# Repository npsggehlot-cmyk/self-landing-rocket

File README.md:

# Self-Landing TVC Rocket

This is my build log and source repository for a 3-inch model rocket that steers itself with a thrust-vectored motor and is designed to land on its own legs. Everything is here: the custom flight computer (RocketFC), the 3D-printed avionics bay, the servo-driven parachute ejector, the flight software, and the simulators I use to test ideas before flying them.

**Current status:** Flight computer v2.1 is ordered from JLCPCB, fully assembled. The firmware is written and has been tested in simulation. The avionics bay and chute ejector are designed and ready to print. Next up is bench testing once the boards arrive, followed by a first flight using the parachute.

| Flight computer (top) | Avionics bay | 3D flight simulator |
|---|---|---|
|  |  |  |

---

## Mission profile

```mermaid
flowchart LR
    A[On the pad<br/>self-test beeps] -->|F15 #1 lit by<br/>launch controller| B[Boost<br/>TVC holds vertical]
    B -->|burnout at ~3.5 s| C[Coast]
    C -->|apogee| D{Flight mode}
    D -->|chute test| E[Servo releases the<br/>spring ejector and chute]
    D -->|landing| F[Free fall]
    F -->|timed so the burn<br/>ends at the ground| G[F15 #2 landing burn<br/>TVC on, legs released]
    E --> H[Legs released below 20 m]
    G --> I[Touchdown<br/>log closed, locator beeps]
    H --> I
```

## What's in this repo

| Folder | Contents | Start here |
|---|---|---|
| [`hardware/flight-computer`](hardware/flight-computer) | RocketFC v2.1, a 70 mm round 4-layer PCB designed in KiCad | `rocket_fc.kicad_pro`, plus Gerbers, BOM and CPL in `fabrication/` |
| [`hardware/avionics-bay`](hardware/avionics-bay) | Printed sled for the Apogee 3" tube, held in place by 8 radial M3 screws | STL and STEP files, tube drill template |
| [`hardware/chute-ejector`](hardware/chute-ejector) | Spring-loaded piston released by a servo-driven latch | Print-ready STLs |
| [`firmware/RocketFC`](firmware/RocketFC) | Arduino Nano flight software: TVC control, flight events, SD logging | `RocketFC.ino` |
| [`simulation/matlab`](simulation/matlab) | Interactive 3D flight simulator for tuning the PID gains and landing delay | `rocketSim3D.m` |
| [`simulation/firmware-sim`](simulation/firmware-sim) | Runs the actual flight firmware on a PC against simulated sensors | `sim.cpp` |
| [`LOG.md`](LOG.md) | Engineering log with a dated entry for each work session | |

## Flight computer overview

```
2S LiPo (XT30) ──┬── diode ── POWER switch ── Nano VIN + 3.3 V (sensors, SD card)
                 ├── 5 V 3 A buck, enabled by the switch ── 3 servos + buzzer
                 └── ARM plug (XT30) ── 4 low-side pyro channels (WAGO lever terminals)
```

| Function | Nano pin | Notes |
|---|---|---|
| Pyro P1 ascent, P2 landing, P3 legs, P4 spare | D2, D4, D6, D8 | AO3400A MOSFETs with 100k gate pull-downs; only live when the ARM plug is in |
| Continuity P1 to P4 | A0 to A3 | About 2.1 V when armed with an igniter connected, about 1.2 V when disarmed, 0 V when open |
| Servo X, servo Y (TVC), AUX (chute) | D3, D5, D7 | Powered from a separate 5 V buck converter |
| Battery and arm sense | A6, A7 | Battery voltage = A6 reading × 4.03 |
| IMU LSM6DSO32 (±32 g) and barometer MS5607 | I²C at 0x6A and 0x77 | Level-shifted to the 5 V Nano |
| microSD card (hinged lid) | SPI, D10 to D13 | Buffered through a 74LVC125 |
| Buzzer | D9 | Magnetic transducer, so it needs a tone rather than a steady signal |

Before ordering, the design passed a full design rule check with no errors, a pad-by-pad comparison between the schematic and the PCB (282 of 282 connections matched), an electrical rules check with no errors, and all 34 BOM lines were matched to parts in stock at JLCPCB.

## Key numbers

| | |
|---|---|
| Body tube | Apogee 3" (74.47 mm inner diameter); the bay and sled are 74.0 mm |
| Motors | 2 × Estes F15 (49.6 N·s total impulse, 25.3 N peak, 3.45 s burn) |
| Battery | 2S LiPo, 1000 mAh, 70 × 35 × 18 mm, XT30 connector |
| Simulated apogee at 1.0 kg | About 50 m |
| Best simulated landing delay | 1.76 s after apogee, with a window of roughly ±0.01 s |

## Links

- Onshape model of the avionics bay: [RocketFC Avionics Bay (3in Apogee tube)](https://cad.onshape.com/documents/a77bffe2781b56247ce74af7/w/bac2e3535b987d098c97ed26/e/773c68a36321aff5911a4cc4)

## Roadmap

- [x] Design, verify and order the flight computer PCB
- [x] Design the avionics bay and chute ejector
- [x] Write the firmware, compile it for the ATmega328P and test it in simulation
- [x] Build the 3D flight simulator in MATLAB
- [ ] Bench test the boards when they arrive: sensors, servos, and a pyro test with a small bulb
- [ ] Print the bay and ejector and test fit them in the tube
- [ ] Static test to measure the F15 igniter delay (`fire2` command)
- [ ] Flight 1: parachute mode with TVC on the way up
- [ ] Tune the PID gains using the flight logs
- [ ] Flight 2 and beyond: propulsive landing attempts

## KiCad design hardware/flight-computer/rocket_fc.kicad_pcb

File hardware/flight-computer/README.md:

# RocketFC v2.1 flight computer PCB

Open `rocket_fc.kicad_pro` in KiCad 7 or newer.

- `fabrication/` holds exactly what was sent to JLCPCB: the Gerbers plus the full-assembly BOM and CPL files.
- `scripts/` has the Python scripts used to generate the schematic and board. `design.py` is the single source of truth for every part and net.
- `lib/` contains a local footprint for the WAGO 2601 lever terminals.

JLCPCB settings used: 4 layers, 1.6 mm, ENIG, Standard PCBA, assembly on both sides, parts placement confirmation, and depaneling.

When bringing up a new board, check the test pads first. VLOG should read about 7.9 V, VSRV 5.0 V and 3V3 3.3 V.

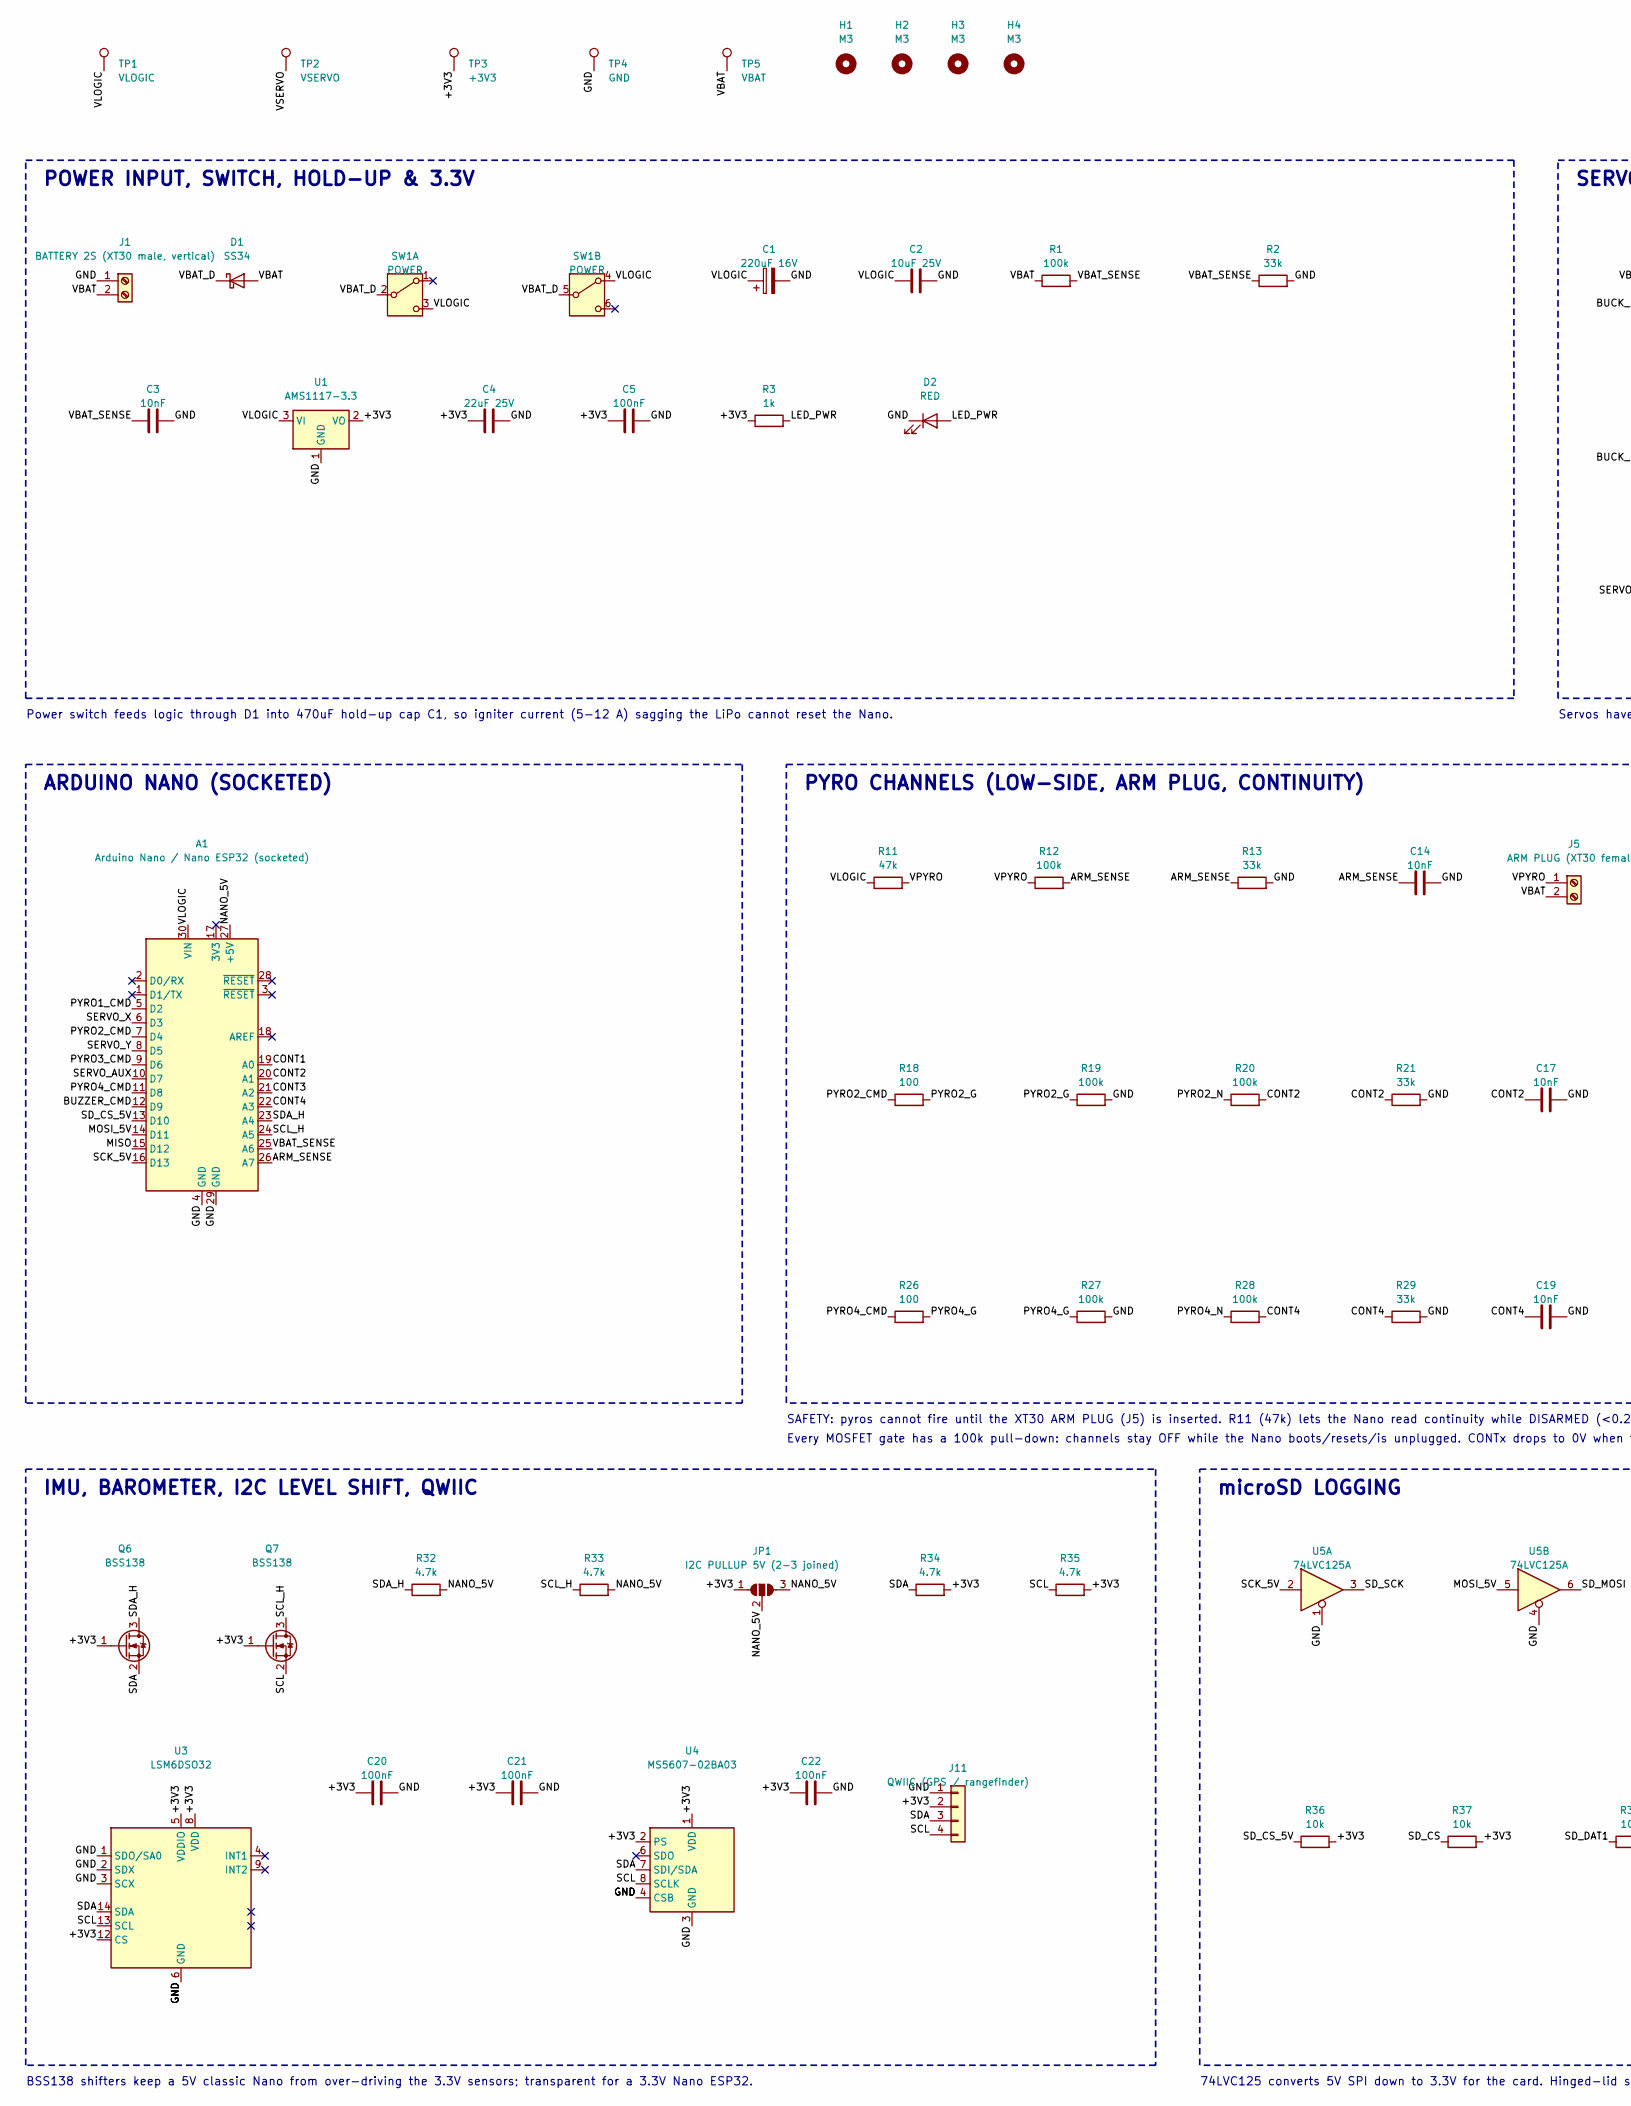
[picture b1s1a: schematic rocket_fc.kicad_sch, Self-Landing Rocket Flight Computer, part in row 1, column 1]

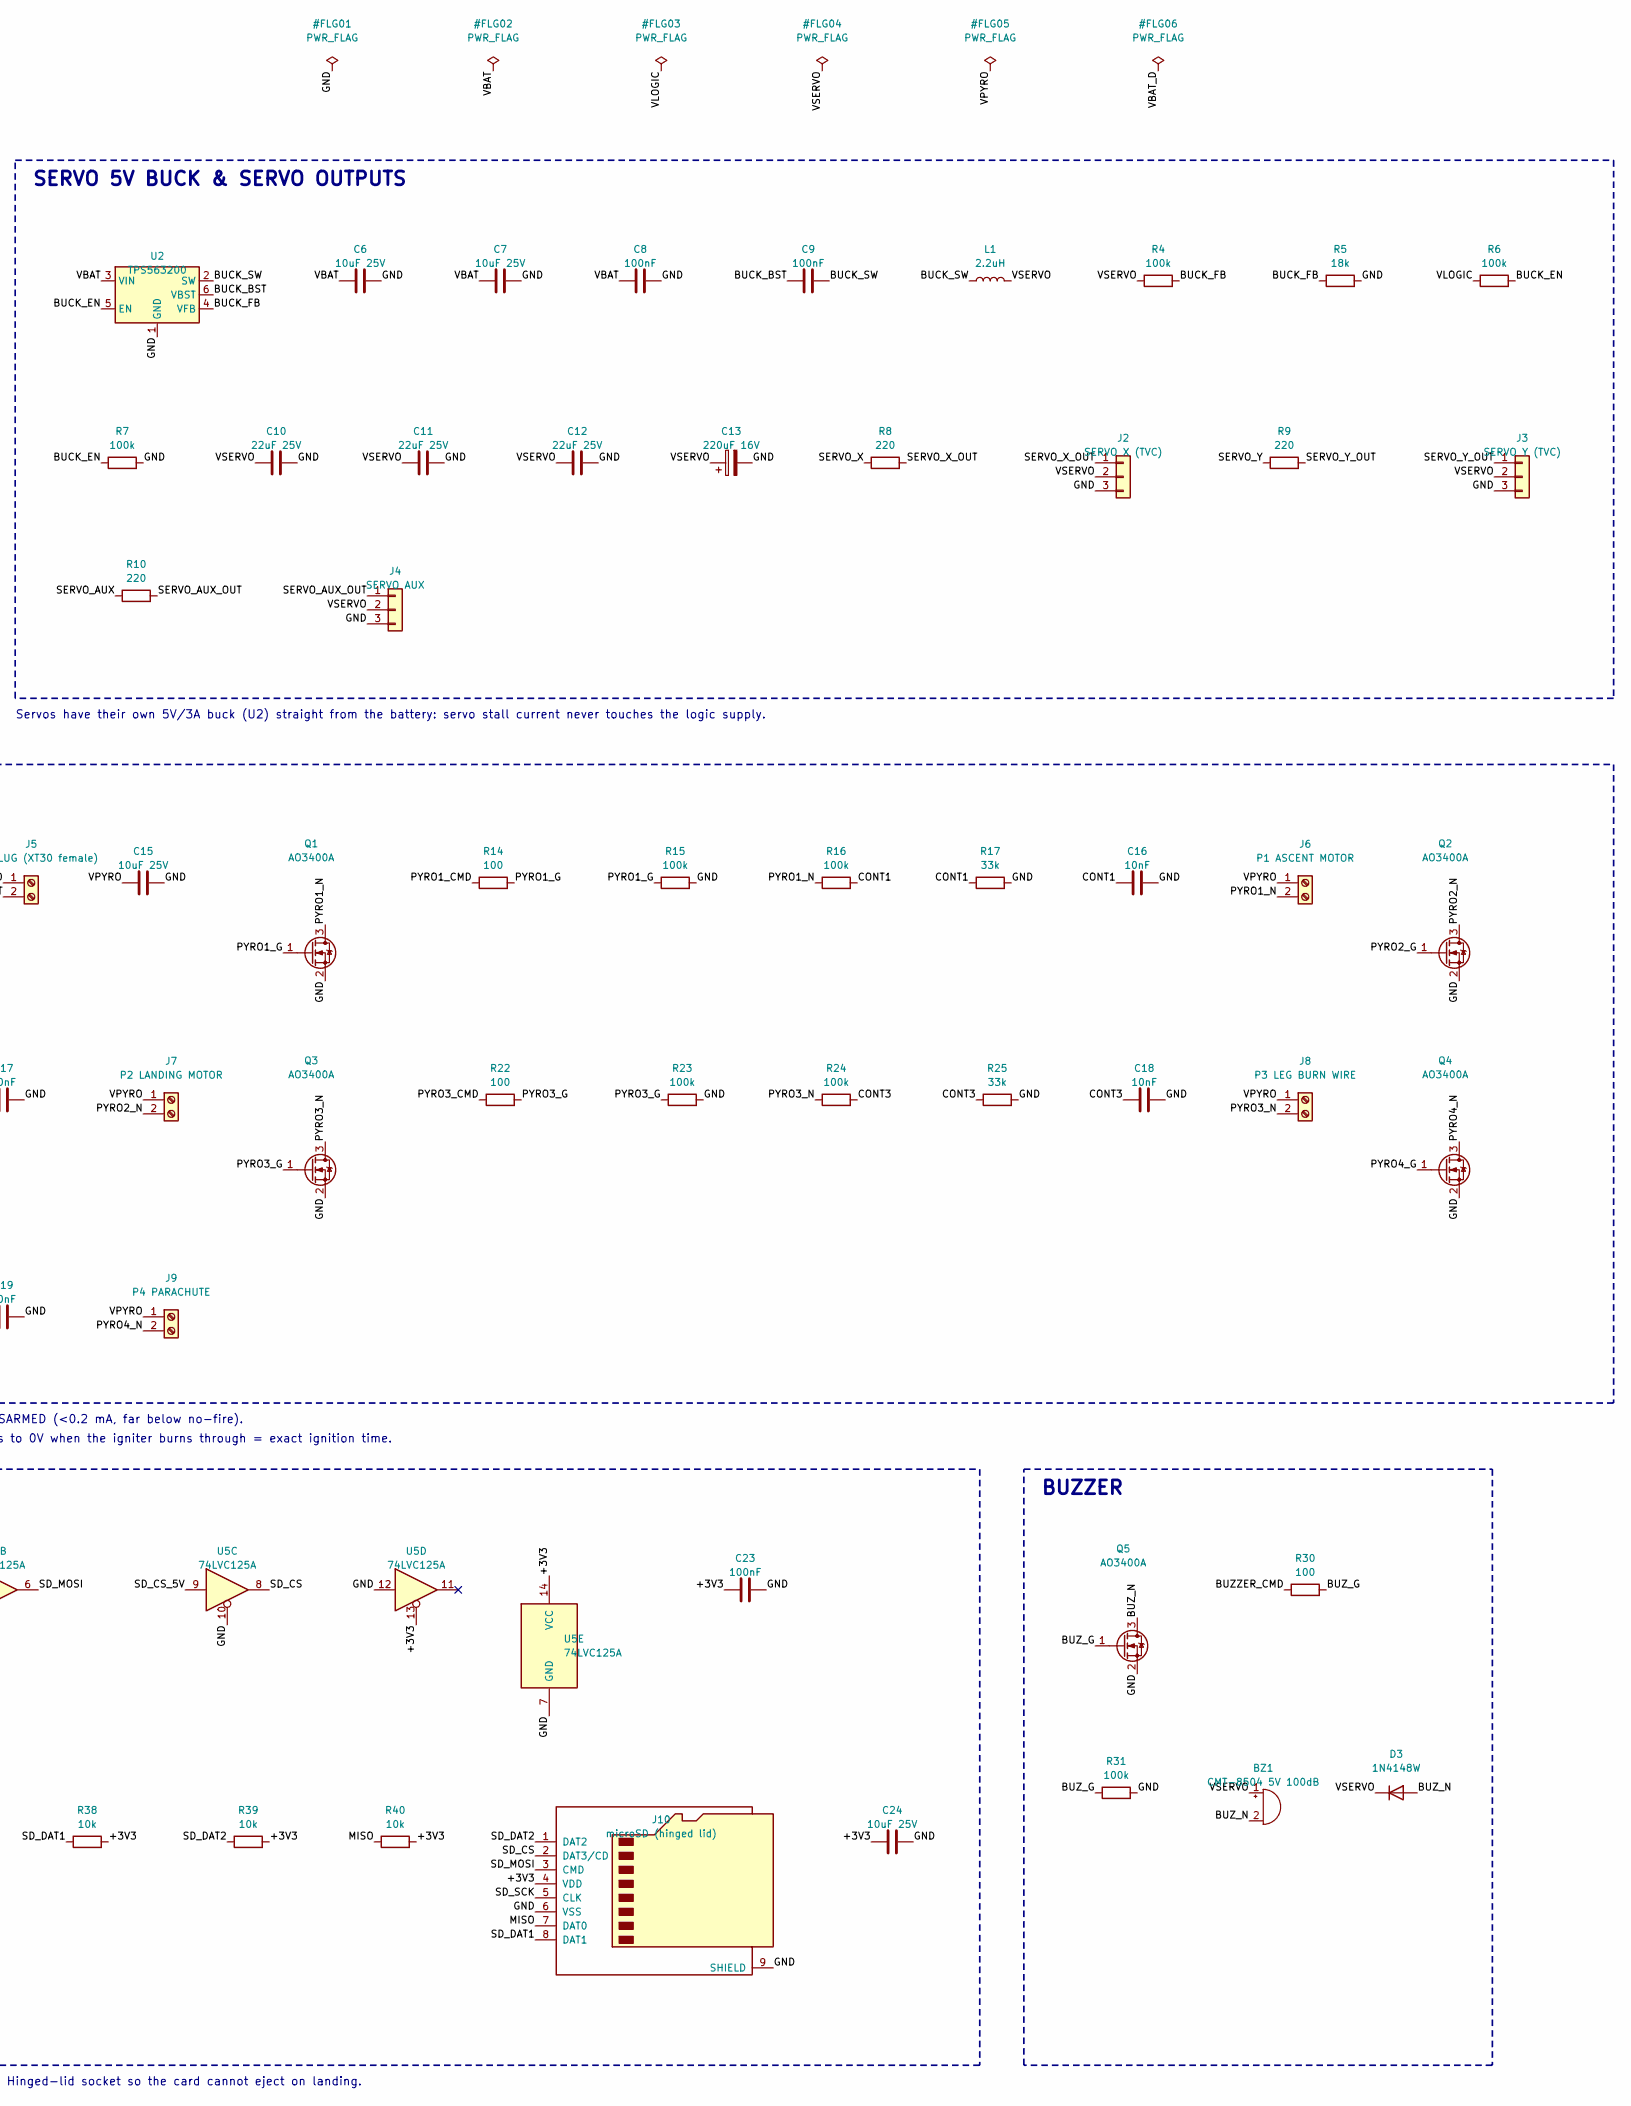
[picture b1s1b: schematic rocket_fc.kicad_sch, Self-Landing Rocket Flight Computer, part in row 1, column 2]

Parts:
A1: Arduino Nano / Nano ESP32 (socketed); Arduino_Nano; MPN 2x 1x15 2.54mm female header (socket)
BZ1: CMT-8504 5V 100dB; MagneticBuzzer_CUI_CMT-8504-100-SMT; MPN Same Sky (CUI) CMT-8504-100-SMT-TR magn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; LCSC C22359707
C1: 220uF 16V; CP_Elec_6.3x7.7; MPN Panasonic EEE-FK1C221P 220uF 16V (brown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; LCSC C178534
C2, C6, C7, C15, C24: 10uF 25V; C_0805_2012Metric; LCSC C15850
C3, C14, C16, C17, C18, C19: 10nF; C_0603_1608Metric; LCSC C57112
C4, C10, C11, C12: 22uF 25V; C_0805_2012Metric; LCSC C45783
C5, C8, C9, C20, C21, C22, C23: 100nF; C_0603_1608Metric; LCSC C14663
C13: 220uF 16V; CP_Elec_6.3x7.7; MPN Panasonic EEE-FK1C221P 220uF 16V (servo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; LCSC C178534
D1: SS34; D_SMA; MPN SS34 (40V 3A Schottky); LCSC C8678
D2: RED; LED_0603_1608Metric; MPN KT-0603R red LED; LCSC C2286
D3: 1N4148W; D_SOD-123; MPN 1N4148W; LCSC C81598
H1, H2, H3, H4: M3; MountingHole_3.2mm_M3
J1: BATTERY 2S (XT30 male, vertical); AMASS_XT30UPB-M_1x02_P5.0mm_Vertical; MPN AMASS XT30UPB-M; LCSC C428721
J2: SERVO X (TVC); PinHeader_1x03_P2.54mm_Vertical; MPN 2.54mm 1x3 male header; LCSC C49257
J3: SERVO Y (TVC); PinHeader_1x03_P2.54mm_Vertical; MPN 2.54mm 1x3 male header; LCSC C49257
J4: SERVO AUX; PinHeader_1x03_P2.54mm_Vertical; MPN 2.54mm 1x3 male header; LCSC C49257
J5: ARM PLUG (XT30 female); AMASS_XT30PW-F_1x02_P2.50mm_Horizontal; MPN AMASS XT30PW-F; LCSC C2913282
J6: P1 ASCENT MOTOR; TerminalBlock_WAGO_2601-3102_1x02_P3.50mm_Vertical; MPN WAGO 2601-3102 (lever); LCSC C20252913
J7: P2 LANDING MOTOR; TerminalBlock_WAGO_2601-3102_1x02_P3.50mm_Vertical; MPN WAGO 2601-3102 (lever); LCSC C20252913
J8: P3 LEG BURN WIRE; TerminalBlock_WAGO_2601-3102_1x02_P3.50mm_Vertical; MPN WAGO 2601-3102 (lever); LCSC C20252913
J9: P4 PARACHUTE; TerminalBlock_WAGO_2601-3102_1x02_P3.50mm_Vertical; MPN WAGO 2601-3102 (lever); LCSC C20252913
J10: microSD (hinged lid); microSD_HC_Molex_47219-2001; MPN Molex 47219-2001 (hinge lid - will not 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; LCSC C164170
J11: QWIIC (GPS / rangefinder); JST_SH_SM04B-SRSS-TB_1x04-1MP_P1.00mm_Horizontal; MPN JST SM04B-SRSS-TB; LCSC C160404
JP1: I2C PULLUP 5V (2-3 joined); SolderJumper-3_P1.3mm_Open_RoundedPad1.0x1.5mm; MPN solder jumper (no part)
L1: 2.2uH; L_Bourns_SRN6045TA; MPN Bourns SRN6045TA-2R2Y (2.2uH, 6A); LCSC C1332316
Q1, Q2, Q3, Q4, Q5: AO3400A; SOT-23; MPN AO3400A; LCSC C20917
Q6, Q7: BSS138; SOT-23; MPN Diodes BSS138-7-F; LCSC C40912
R1, R4, R6, R7, R12, R15, R16, R19, R20, R23, R24, R27, R28, R31: 100k; R_0603_1608Metric; LCSC C25803
R2, R13, R17, R21, R25, R29: 33k; R_0603_1608Metric; LCSC C4216
R3: 1k; R_0603_1608Metric; LCSC C21190
R5: 18k; R_0603_1608Metric; LCSC C25810
R8, R9, R10: 220; R_0603_1608Metric; LCSC C22962
R11: 47k; R_0603_1608Metric; LCSC C25819
R14, R18, R22, R26, R30: 100; R_0603_1608Metric; LCSC C22775
R32, R33, R34, R35: 4.7k; R_0603_1608Metric; LCSC C23162
R36, R37, R38, R39, R40: 10k; R_0603_1608Metric; LCSC C25804
SW1: POWER; SW_CK_JS202011AQN_DPDT_Angled; MPN C&K JS202011AQN; LCSC C221662
TP1: VLOGIC; TestPoint_Pad_D1.5mm
TP2: VSERVO; TestPoint_Pad_D1.5mm
TP3: +3V3; TestPoint_Pad_D1.5mm
TP4: GND; TestPoint_Pad_D1.5mm
TP5: VBAT; TestPoint_Pad_D1.5mm
U1: AMS1117-3.3; SOT-223-3_TabPin2; MPN AMS1117-3.3; LCSC C6186
U2: TPS563200; SOT-23-6; MPN TI TPS563200DDCR; LCSC C97253
U3: LSM6DSO32; LGA-14_3x2.5mm_P0.5mm_LayoutBorder3x4y; MPN ST LSM6DSO32TR (+/-32g, 2000dps; pin-co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; LCSC C1864162
U4: MS5607-02BA03; LGA-8_3x5mm_P1.25mm; MPN TE MS5607-02BA03 (pin-compatible MS5611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; LCSC C97627
U5: 74LVC125A; SOIC-14_3.9x8.7mm_P1.27mm; MPN TI SN74LVC125ADR (5V-tolerant inputs, r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; LCSC C7661

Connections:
+3V3: C4.1, C5.1, C20.1, C21.1, C22.1, C23.1, C24.1, J10.4 (VDD), J11.2, JP1.1 (A), Q6.1 (G), Q7.1 (G), R3.1, R34.2, R35.2, R36.2, R37.2, R38.2, R39.2, R40.2, TP3.1, U1.2 (VO), U3.5 (VDDIO), U3.8 (VDD), U3.12 (CS), U4.1 (VDD), U4.2 (PS), U5.13, U5.14 (VCC)
ARM_SENSE: A1.26 (A7), C14.1, R12.2, R13.1
BUCK_BST: C9.1, U2.6 (VBST)
BUCK_EN: R6.2, R7.1, U2.5 (EN)
BUCK_FB: R4.2, R5.1, U2.4 (VFB)
BUCK_SW: C9.2, L1.1, U2.2 (SW)
BUZZER_CMD: A1.12 (D9), R30.1
BUZ_G: Q5.1 (G), R30.2, R31.1
BUZ_N: BZ1.2 (-), D3.2 (A), Q5.3 (D)
CONT1: A1.19 (A0), C16.1, R16.2, R17.1
CONT2: A1.20 (A1), C17.1, R20.2, R21.1
CONT3: A1.21 (A2), C18.1, R24.2, R25.1
CONT4: A1.22 (A3), C19.1, R28.2, R29.1
GND: A1.4 (GND), A1.29 (GND), C1.2, C2.2, C3.2, C4.2, C5.2, C6.2, C7.2, C8.2, C10.2, C11.2, C12.2, C13.2, C14.2, C15.2, C16.2, C17.2, C18.2, C19.2, C20.2, C21.2, C22.2, C23.2, C24.2, D2.1 (K), J1.1, J2.3, J3.3, J4.3, J10.6 (VSS), J10.9 (SHIELD), J11.1, Q1.2 (S), Q2.2 (S), Q3.2 (S), Q4.2 (S), Q5.2 (S), R2.2, R5.2, R7.2, R13.2, R15.2, R17.2, R19.2, R21.2, R23.2, R25.2, R27.2, R29.2, R31.2, TP4.1, U1.1 (GND), U2.1 (GND), U3.1 (SDO/SA0), U3.2 (SDX), U3.3 (SCX), U3.6 (GND), U3.7 (GND), U4.3 (GND), U4.4 (CSB), U4.5 (CSB), U5.1, U5.4, U5.7 (GND), U5.10, U5.12
LED_PWR: D2.2 (A), R3.2
MISO: A1.15 (D12), J10.7 (DAT0), R40.1
MOSI_5V: A1.14 (D11), U5.5
NANO_5V: A1.27 (+5V), JP1.2 (C), JP1.3 (B), R32.2, R33.2
PYRO1_CMD: A1.5 (D2), R14.1
PYRO1_G: Q1.1 (G), R14.2, R15.1
PYRO1_N: J6.2, Q1.3 (D), R16.1
PYRO2_CMD: A1.7 (D4), R18.1
PYRO2_G: Q2.1 (G), R18.2, R19.1
PYRO2_N: J7.2, Q2.3 (D), R20.1
PYRO3_CMD: A1.9 (D6), R22.1
PYRO3_G: Q3.1 (G), R22.2, R23.1
PYRO3_N: J8.2, Q3.3 (D), R24.1
PYRO4_CMD: A1.11 (D8), R26.1
PYRO4_G: Q4.1 (G), R26.2, R27.1
PYRO4_N: J9.2, Q4.3 (D), R28.1
SCK_5V: A1.16 (D13), U5.2
SCL: J11.4, Q7.2 (S), R35.1, U3.13 (SCL), U4.8 (SCLK)
SCL_H: A1.24 (A5), Q7.3 (D), R33.1
SDA: J11.3, Q6.2 (S), R34.1, U3.14 (SDA), U4.7 (SDI/SDA)
SDA_H: A1.23 (A4), Q6.3 (D), R32.1
SD_CS: J10.2 (DAT3/CD), R37.1, U5.8
SD_CS_5V: A1.13 (D10), R36.1, U5.9
SD_DAT1: J10.8 (DAT1), R38.1
SD_DAT2: J10.1 (DAT2), R39.1
SD_MOSI: J10.3 (CMD), U5.6
SD_SCK: J10.5 (CLK), U5.3
SERVO_AUX: A1.10 (D7), R10.1
SERVO_AUX_OUT: J4.1, R10.2
SERVO_X: A1.6 (D3), R8.1
SERVO_X_OUT: J2.1, R8.2
SERVO_Y: A1.8 (D5), R9.1
SERVO_Y_OUT: J3.1, R9.2
VBAT: C6.1, C7.1, C8.1, D1.2 (A), J1.2, J5.2, R1.1, TP5.1, U2.3 (VIN)
VBAT_D: D1.1 (K), SW1.2 (B), SW1.5 (B)
VBAT_SENSE: A1.25 (A6), C3.1, R1.2, R2.1
VLOGIC: A1.30 (VIN), C1.1, C2.1, R6.1, R11.1, SW1.3 (C), SW1.4 (A), TP1.1, U1.3 (VI)
VPYRO: C15.1, J5.1, J6.1, J7.1, J8.1, J9.1, R11.2, R12.1
VSERVO: BZ1.1 (+), C10.1, C11.1, C12.1, C13.1, D3.1 (K), J2.2, J3.2, J4.2, L1.2, R4.1, TP2.1

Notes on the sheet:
POWER INPUT, SWITCH, HOLD-UP & 3.3V
SERVO 5V BUCK & SERVO OUTPUTS
ARDUINO NANO (SOCKETED)
PYRO CHANNELS (LOW-SIDE, ARM PLUG, CONTINUITY)
IMU, BAROMETER, I2C LEVEL SHIFT, QWIIC
microSD LOGGING
BUZZER
SAFETY: pyros cannot fire until the XT30 ARM PLUG (J5) is inserted. R11 (47k) lets the Nano read continuity while DISARMED (<0.2 mA, far below no-fire).
Every MOSFET gate has a 100k pull-down: channels stay OFF while the Nano boots/resets/is unplugged. CONTx drops to 0V when the igniter burns through = exact ignition time.
Power switch feeds logic through D1 into 470uF hold-up cap C1, so igniter current (5-12 A) sagging the LiPo cannot reset the Nano.
Servos have their own 5V/3A buck (U2) straight from the battery: servo stall current never touches the logic supply.
BSS138 shifters keep a 5V classic Nano from over-driving the 3.3V sensors; transparent for a 3.3V Nano ESP32.
74LVC125 converts 5V SPI down to 3.3V for the card. Hinged-lid socket so the card cannot eject on landing.

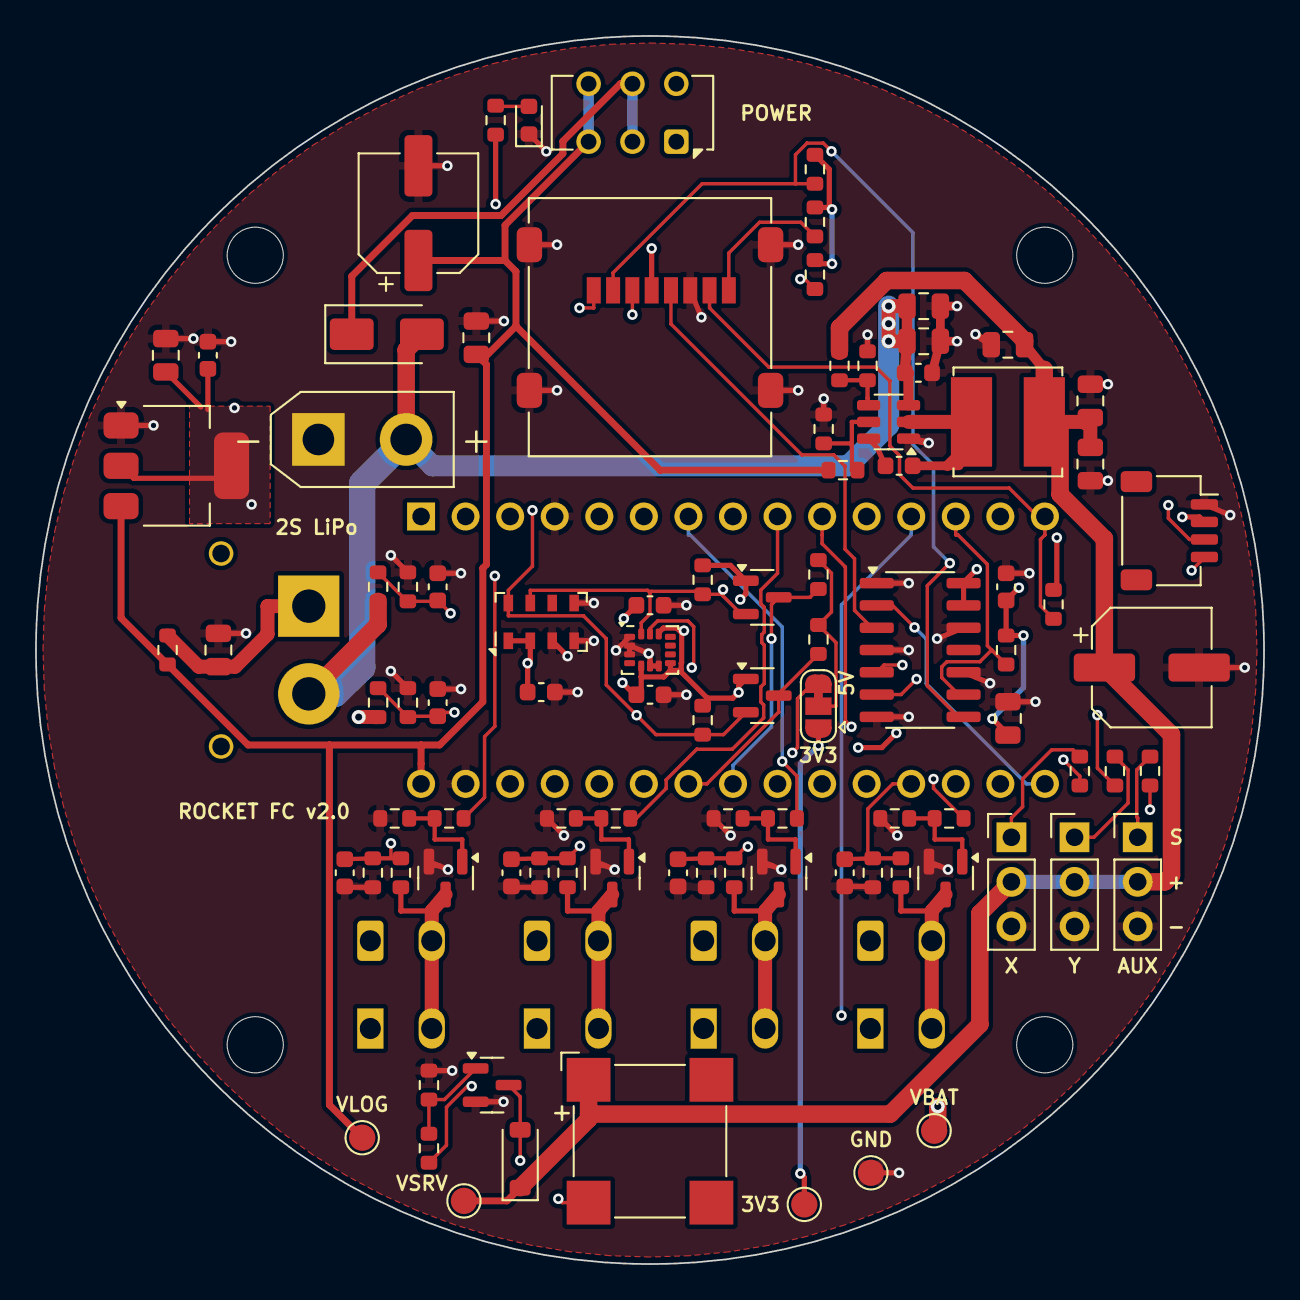
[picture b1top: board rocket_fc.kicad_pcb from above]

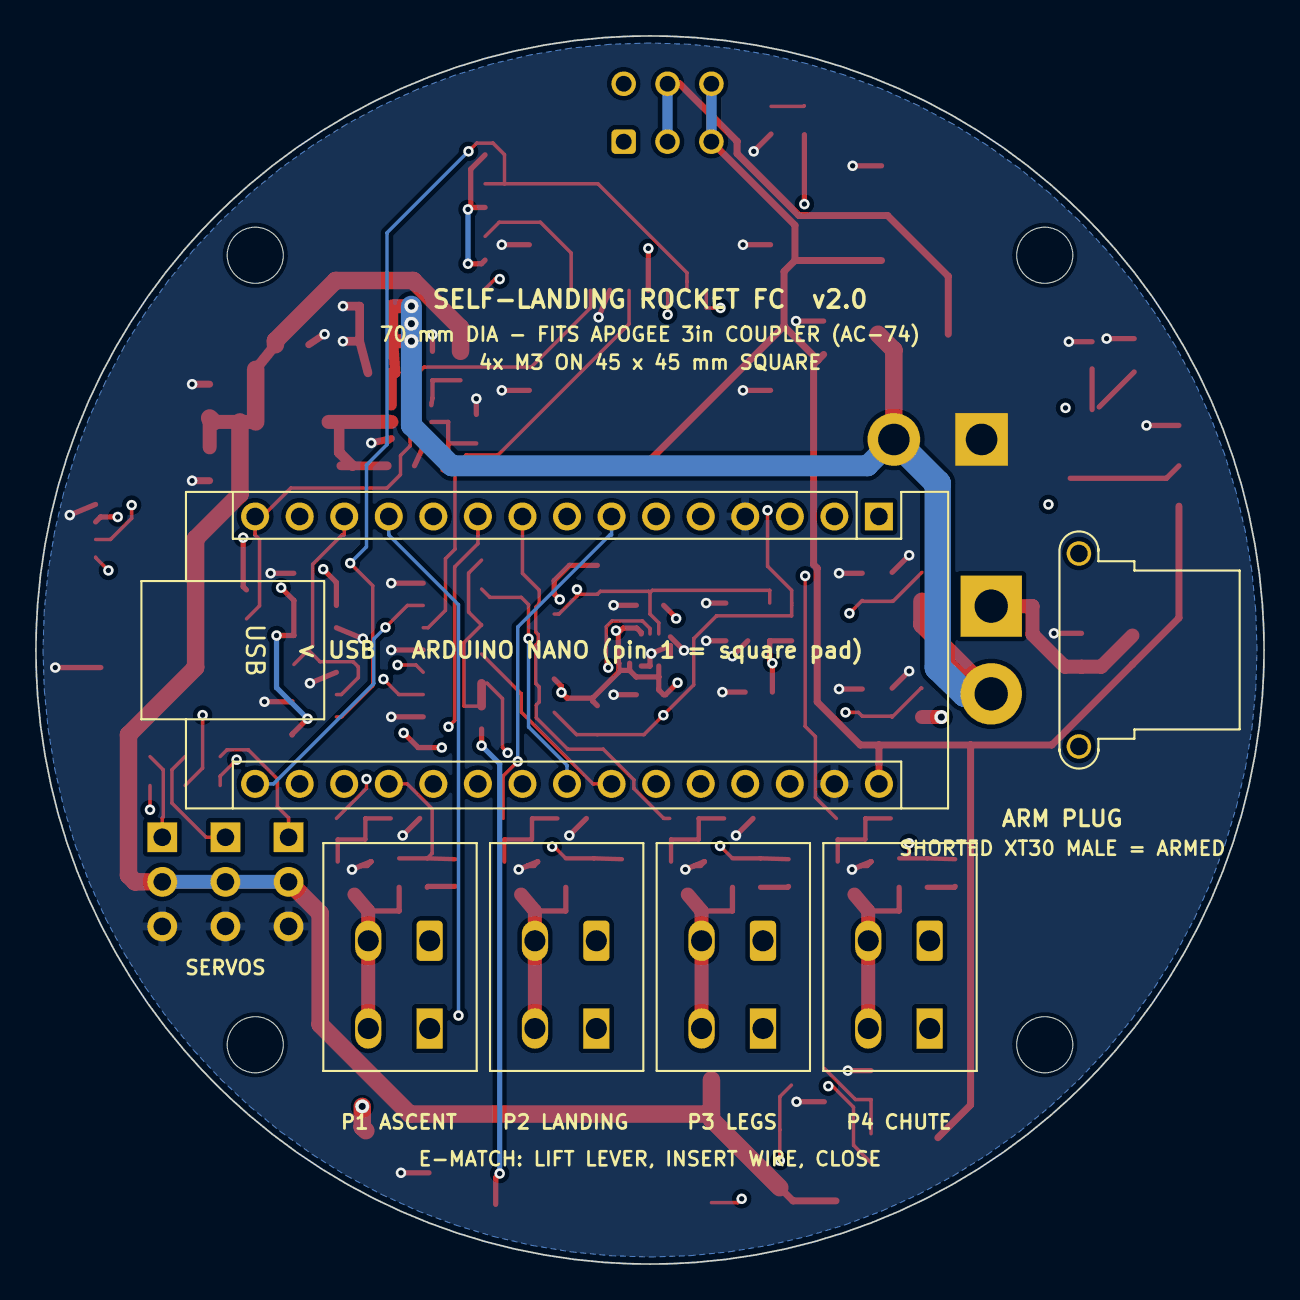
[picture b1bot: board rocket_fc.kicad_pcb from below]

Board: 4 copper layers, 70.0 x 70.0 mm, 104 parts (6 on the bottom side), 53 nets.

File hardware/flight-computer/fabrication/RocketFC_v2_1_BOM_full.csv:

Comment,Designator,Footprint,LCSC Part #
CMT-8504 5V 100dB,BZ1,MagneticBuzzer_CUI_CMT-8504-100-SMT,C22359707
220uF 16V,"C1,C13",CP_Elec_6.3x7.7,C178534
10uF 25V,"C2,C6,C7,C15,C24",C_0805_2012Metric,C15850
10nF,"C3,C14,C16,C17,C18,C19",C_0603_1608Metric,C57112
22uF 25V,"C4,C10,C11,C12",C_0805_2012Metric,C45783
100nF,"C5,C8,C9,C20,C21,C22,C23",C_0603_1608Metric,C14663
SS34,D1,D_SMA,C8678
RED,D2,LED_0603_1608Metric,C2286
1N4148W,D3,D_SOD-123,C81598
"BATTERY 2S (XT30 male, vertical)",J1,AMASS_XT30UPB-M_1x02_P5.0mm_Vertical,C428721
2.54mm 1x3 male header,"J2,J3,J4",PinHeader_1x03_P2.54mm_Vertical,C49257
ARM PLUG (XT30 female),J5,AMASS_XT30PW-F_1x02_P2.50mm_Horizontal,C2913282
WAGO 2601-3102 (lever),"J6,J7,J8,J9",TerminalBlock_WAGO_2601-3102_1x02_P3.50mm_Vertical,C20252913
microSD (hinged lid),J10,microSD_HC_Molex_47219-2001,C164170
QWIIC (GPS / rangefinder),J11,JST_SH_SM04B-SRSS-TB_1x04-1MP_P1.00mm_Horizontal,C160404
2.2uH,L1,L_Bourns_SRN6045TA,C1332316
AO3400A,"Q1,Q2,Q3,Q4,Q5",SOT-23,C20917
BSS138,"Q6,Q7",SOT-23,C40912
100k,"R1,R4,R6,R7,R12,R15,R16,R19,R20,R23,R24,R27,R28,R31",R_0603_1608Metric,C25803
33k,"R2,R13,R17,R21,R25,R29",R_0603_1608Metric,C4216
1k,R3,R_0603_1608Metric,C21190
18k,R5,R_0603_1608Metric,C25810
220,"R8,R9,R10",R_0603_1608Metric,C22962
47k,R11,R_0603_1608Metric,C25819
100,"R14,R18,R22,R26,R30",R_0603_1608Metric,C22775
4.7k,"R32,R33,R34,R35",R_0603_1608Metric,C23162
10k,"R36,R37,R38,R39,R40",R_0603_1608Metric,C25804
POWER,SW1,SW_CK_JS202011AQN_DPDT_Angled,C221662
AMS1117-3.3,U1,SOT-223-3_TabPin2,C6186
TPS563200,U2,SOT-23-6,C97253
LSM6DSO32,U3,LGA-14_3x2.5mm_P0.5mm_LayoutBorder3x4y,C1864162
MS5607-02BA03,U4,LGA-8_3x5mm_P1.25mm,C97627
74LVC125A,U5,SOIC-14_3.9x8.7mm_P1.27mm,C7661
Nano socket 1x15 female 2.54mm,"A1_S1,A1_S2",PinSocket_1x15_P2.54mm_Vertical,C41417327

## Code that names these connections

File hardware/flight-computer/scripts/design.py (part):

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P('C13', 'Device:C_Polarized', '220uF 16V', 'Capacitor_SMD:CP_Elec_6.3x7.7',
  {'1': 'VSERVO', '2': 'GND'}, 'servo', mpn='Panasonic EEE-FK1C221P 220uF 16V (servo bulk)')

for i, (sig, pin) in enumerate([('SERVO_X', 'D3'), ('SERVO_Y', 'D5'), ('SERVO_AUX', 'D7')]):
    n = i + 1
    R(f'R{7+n}', '220', f'{sig}', f'{sig}_OUT', 'servo')
    P(f'J{1+n}', 'Connector_Generic:Conn_01x03', ['SERVO X (TVC)', 'SERVO Y (TVC)', 'SERVO AUX'][i],
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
